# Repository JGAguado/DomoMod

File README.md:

[![GitHub Release][releases-shield]][releases]
[![License][license-shield]](LICENSE)

[![Project Maintenance][maintenance-shield]][maintenance]
[![BuyMeCoffee][buymecoffee-shield]][buymecoffee]

# DomoMod
Mod for ArduLab, directly plugable via the Mod Interface. The DomoMod is designed to enhance the ArduLab functions for domotics aplications: environment monitoring and security systems.

## Project tree

<li><a href="./Design/">Design</a></li>
<li><a href="./Documentation/">Documentation</a></li>

<li><a href="./README.md">README.md</a></li>

[releases-shield]: https://img.shields.io/github/release/JGAguado/DomoMod.svg?style=for-the-badge
[releases]: https://github.com/JGAguado/DomoMod/releases

[license-shield]: https://img.shields.io/badge/License-CC%20BY--NC--SA%204.0-lightgrey.svg?style=for-the-badge

[maintenance-shield]: https://img.shields.io/badge/maintainer-J.%20G.%20Aguado-blue.svg?style=for-the-badge
[maintenance]: https://github.com/JGAguado

[buymecoffee-shield]: https://img.shields.io/badge/buy%20me%20a%20coffee-support-yellow.svg?style=for-the-badge
[buymecoffee]: https://www.buymeacoffee.com/J.G.Aguado

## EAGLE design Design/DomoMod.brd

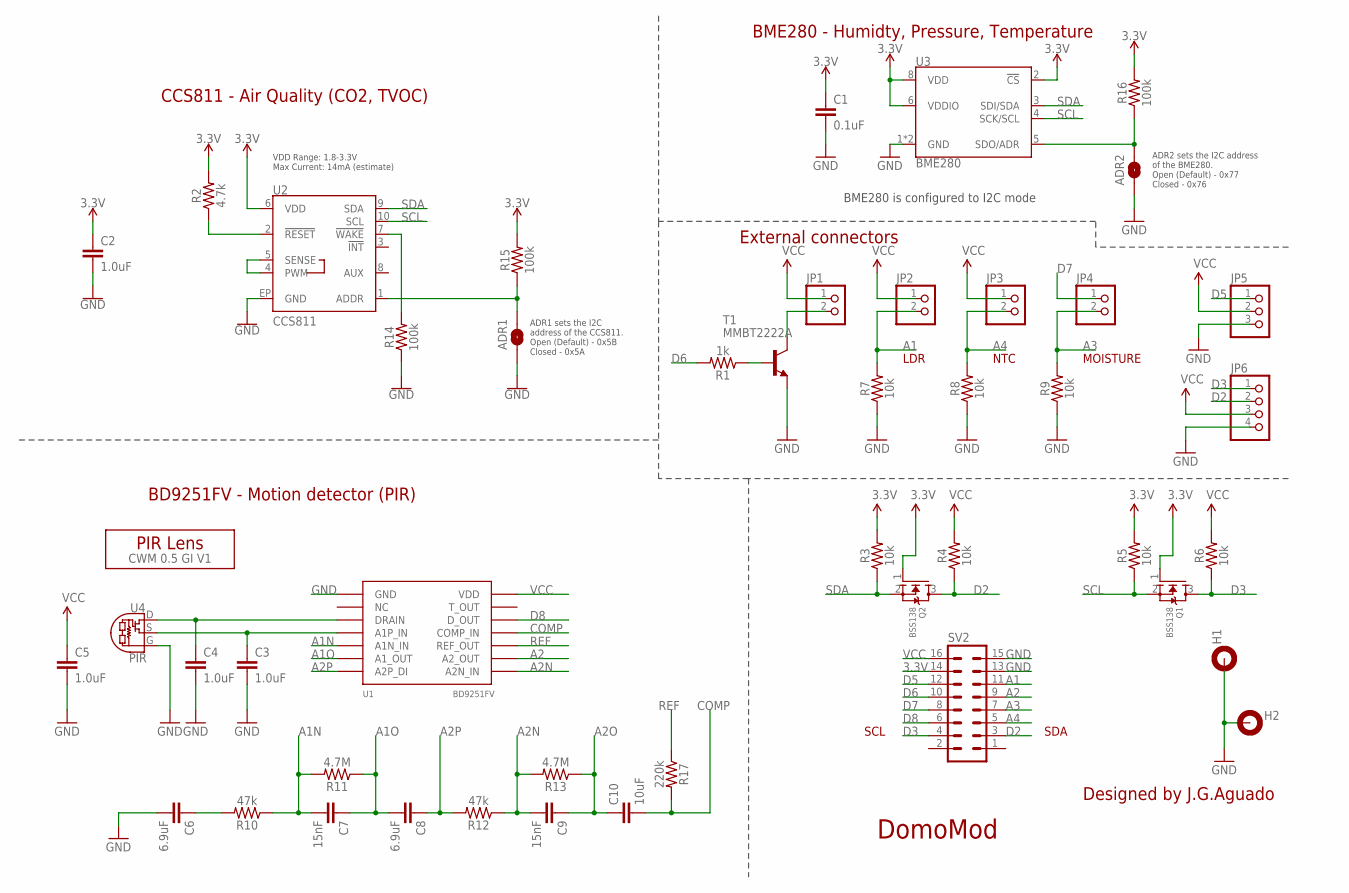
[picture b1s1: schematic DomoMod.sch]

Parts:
ADR1, ADR2: JUMPER-SMT_2_NO_SILK; SMT-JUMPER_2_NO_SILK
C1: 0.1uF; 0603
C2, C3, C4, C5: 1.0uF; 0603
C6, C8: 6.9uF; 0603
C7, C9: 15nF; 0603
C10: 10uF; 0603
H1, H2: MOUNT-PAD-ROUND3.2; 3,2-PAD
JP1, JP2, JP3, JP4: PINHD-1X2; 1X02
JP5: PINHD-1X3; 1X03
JP6: PINHD-1X4; 1X04
Q1, Q2: BSS138; SOT23
R1: 1k; 0603
R2: 4.7k; 0603
R3, R4, R5, R6, R7, R8, R9: 10k; 0603
R10, R12: 47k; 0603
R11, R13: 4.7M; 0603
R14, R15, R16: 100k; 0603
R17: 220k; 0603
SV2: MA08-2
T1: MMBT2222A; SOT23-BEC
U1: BD9251FV; TSSOP-14
U2: CCS811; LGA10
U3: BME280; LGA-8-2.5X2.5
U4: PIR
U$1: CWM 0.5 GI V1; LENS-CWM-0.5-GI-V1

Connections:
3.3V: C1.1, C2.1, Q1.1 (G), Q2.1 (G), R2.2, R3.2, R5.2, R15.2, R16.2, SV2.14, U2.6 (VDD), U3.2 (!CS), U3.6 (VDDIO), U3.8 (VDD)
!RST: R2.1, U2.2 (!RESET!)
!WAKE: R14.2, U2.7 (!WAKE!)
A1: JP2.2, R7.2, SV2.11
A1N: C7.2, R10.1, R11.2, U1.5 (A1N_IN)
A1O: C7.1, C8.2, R11.1, U1.6 (A1_OUT)
A2: SV2.9, U1.9 (A2_OUT)
A2N: C9.2, R12.1, R13.2, U1.8 (A2N_IN)
A2O: C9.1, C10.1, R13.1
A2P: C8.1, R12.2, U1.7 (A2P_DI)
A3: JP4.2, R9.2, SV2.7
A4: JP3.2, R8.2, SV2.5
CCS811_ADDR: ADR1.2, R15.1, U2.1 (ADDR)
COMP: C10.2, R17.2, U1.11 (COMP_IN)
D2: JP6.2, Q2.3 (D), R4.1, SV2.3
D3: JP6.1, Q1.3 (D), R6.1, SV2.4
D5: JP5.1, SV2.12
D6: R1.2, SV2.10
D7: JP4.1, SV2.8
D8: SV2.6, U1.12 (D_OUT)
GND: ADR1.1, ADR2.1, C1.2, C2.2, C3.2, C4.2, C5.2, C6.2, H1.B3,2, H2.B3,2, JP5.3, JP6.4, R7.1, R8.1, R9.1, R14.1, SV2.13, SV2.15, T1.E, U1.1 (GND), U2.EP (GND), U3.1 (GND), U3.7 (GND), U4.G
unnamed: C6.1, R10.2
unnamed: C3.1, U1.4 (A1P_IN), U4.S
unnamed: C4.1, U1.3 (DRAIN), U4.D
unnamed: JP1.2, T1.C
unnamed: R1.1, T1.B
NTC_SENSE: U2.4 (PWM), U2.5 (SENSE)
REF: R17.1, U1.10 (REF_OUT)
SCL: Q1.2 (S), R5.1, U2.10 (SCL), U3.4 (SCK/SCL)
SDA: Q2.2 (S), R3.1, U2.9 (SDA), U3.3 (SDI/SDA)
SDO/ADR: ADR2.2, R16.1, U3.5 (SDO/ADR)
VCC: C5.1, JP1.1, JP2.1, JP3.1, JP5.2, JP6.3, R4.2, R6.2, SV2.16, U1.14 (VDD)

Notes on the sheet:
DomoMod
Designed by J.G.Aguado
VDD Range: 1.8-3.3V Max Current: 14mA (estimate)
CCS811 - Air Quality (CO2, TVOC)
ADR1 sets the I2C address of the CCS811. Open (Default) - 0x5B Closed - 0x5A
ADR2 sets the I2C address of the BME280. Open (Default) - 0x77 Closed - 0x76
BME280 is configured to I2C mode
BME280 - Humidty, Pressure, Temperature
BD9251FV - Motion detector (PIR)
External connectors
SCL
SDA
LDR
NTC
MOISTURE

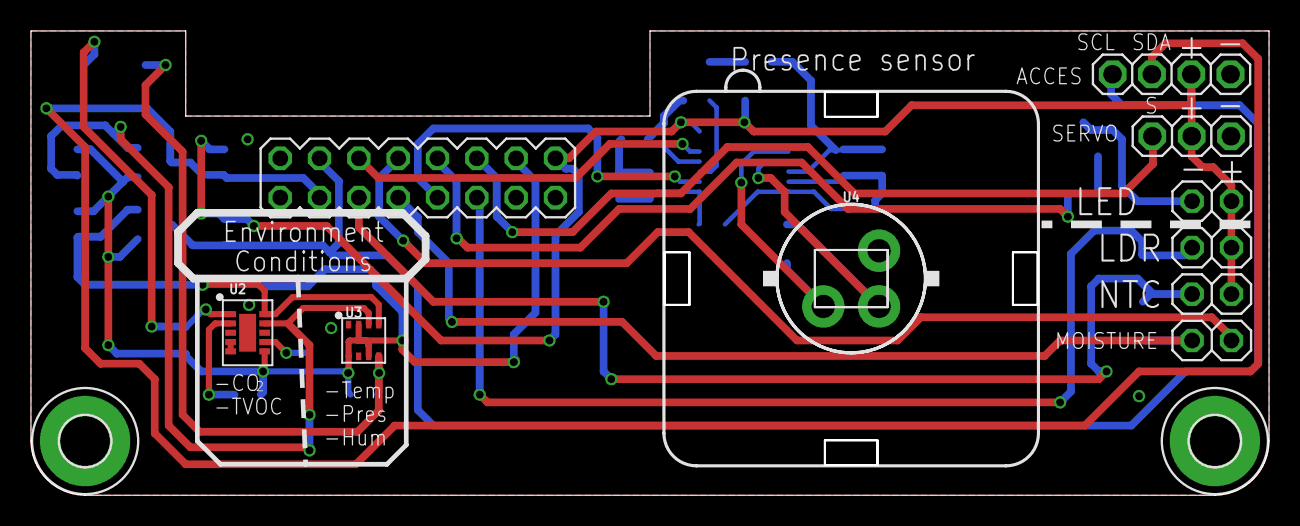
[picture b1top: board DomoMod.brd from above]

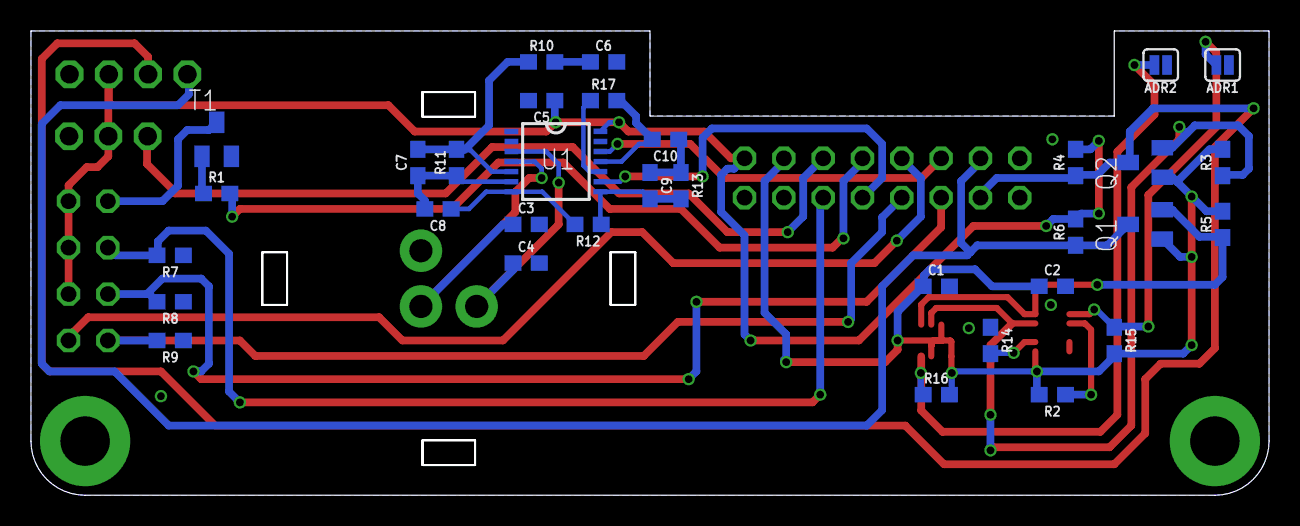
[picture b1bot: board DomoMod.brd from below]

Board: 2 copper layers, 79.9 x 29.9 mm, 46 parts (33 on the bottom side), 32 nets.

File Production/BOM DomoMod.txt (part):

Part Value         Device                    Package              Description                                                MF MPN OC_FARNELL OC_NEWARK PROD_ID   VALUE        
ADR1               JUMPER-SMT_2_NO_SILK      SMT-JUMPER_2_NO_SILK Normally open jumper                                                                                          
ADR2               JUMPER-SMT_2_NO_SILK      SMT-JUMPER_2_NO_SILK Normally open jumper                                                                                          
C1   0.1uF         0.1UF-0603-25V-(+80/-20%) 0603                 0.1µF ceramic capacitors                                                               CAP-00810 0.1uF        
C2   1.0uF         1.0UF-0603-16V-10%        0603                 1µF ceramic capacitors                                                                 CAP-00868 1.0uF        
C3   1.0uF         1.0UF-0603-16V-10%        0603                 1µF ceramic capacitors                                                                 CAP-00868 1.0uF        
C4   1.0uF         1.0UF-0603-16V-10%        0603                 1µF ceramic capacitors                                                                 CAP-00868 1.0uF        
C5   1.0uF         1.0UF-0603-16V-10%        0603                 1µF ceramic capacitors                                                                 CAP-00868 1.0uF        
C6   6.9uF         1.0UF-0603-16V-10%        0603                 1µF ceramic capacitors                                                                 CAP-00868 1.0uF        
C7   15nF          1.0UF-0603-16V-10%        0603                 1µF ceramic capacitors                                                                 CAP-00868 1.0uF        
C8   6.9uF         1.0UF-0603-16V-10%        0603                 1µF ceramic capacitors                                                                 CAP-00868 1.0uF        
C9   15nF          1.0UF-0603-16V-10%        0603                 1µF ceramic capacitors                                                                 CAP-00868 1.0uF        
C10  10uF          1.0UF-0603-16V-10%        0603                 1µF ceramic capacitors                                                                 CAP-00868 1.0uF        
H1                 MOUNT-PAD-ROUND3.2        3,2-PAD              MOUNTING PAD, round                                                                                           
H2                 MOUNT-PAD-ROUND3.2        3,2-PAD              MOUNTING PAD, round                                                                                           
JP1                PINHD-1X2                 1X02                 PIN HEADER                                                                                                    
JP2                PINHD-1X2                 1X02                 PIN HEADER                                                                                                    
JP3                PINHD-1X2                 1X02                 PIN HEADER                                                                                                    
JP4                PINHD-1X2                 1X02                 PIN HEADER                                                                                                    
JP5                PINHD-1X3                 1X03                 PIN HEADER                                                                                                    
JP6                PINHD-1X4                 1X04                 PIN HEADER                                                                                                    
Q1   BSS138        MOSFET-NREFLOW            SOT23                N-Channel Mosfet                                                                                              
Q2   BSS138        MOSFET-NREFLOW            SOT23                N-Channel Mosfet                                                                                              
R1   1k            100KOHM-0603-1/10W-1%     0603                 100kO resistor                                                                         RES-07828 100k         
R2   4.7k          4.7KOHM-0603-1/10W-1%     0603                 4.7kO resistor                                                                         RES-07857 4.7k         
R3   10k           100KOHM-0603-1/10W-1%     0603                 100kO resistor                                                                         RES-07828 100k         
R4   10k           100KOHM-0603-1/10W-1%     0603                 100kO resistor                                                                         RES-07828 100k         
R5   10k           100KOHM-0603-1/10W-1%     0603                 100kO resistor                                                                         RES-07828 100k         
R6   10k           100KOHM-0603-1/10W-1%     0603                 100kO resistor                                                                         RES-07828 100k         
R7   10k           100KOHM-0603-1/10W-1%     0603                 100kO resistor                                                                         RES-07828 100k         
R8   10k           100KOHM-0603-1/10W-1%     0603                 100kO resistor                                                                         RES-07828 100k         
R9   10k           100KOHM-0603-1/10W-1%     0603                 100kO resistor                                                                         RES-07828 100k         
R10  47k           100KOHM-0603-1/10W-1%     0603                 100kO resistor                                                                         RES-07828 100k         
R11  4.7M          100KOHM-0603-1/10W-1%     0603                 100kO resistor                                                                         RES-07828 100k         
R12  47k           100KOHM-0603-1/10W-1%     0603                 100kO resistor                                                                         RES-07828 100k         
R13  4.7M          100KOHM-0603-1/10W-1%     0603                 100kO resistor                                                                         RES-07828 100k         
R14  100k          100KOHM-0603-1/10W-1%     0603                 100kO resistor                                                                         RES-07828 100k         
R15  100k          100KOHM-0603-1/10W-1%     0603                 100kO resistor                                                                         RES-07828 100k         
R16  100k          100KOHM-0603-1/10W-1%     0603                 100kO resistor                                                                         RES-07828 100k         
R17  220k          100KOHM-0603-1/10W-1%     0603                 100kO resistor                                                                         RES-07828 100k         
SV1                MA08-2                    MA08-2               PIN HEADER                                                        unknown    unknown                          
T1   MMBT2222A     BC808-NPN-SOT23-BEC       SOT23-BEC            NPN Transistror                                                                                               
U$1  CWM 0.5 GI V1 PIR-LENSCWM-0.5-GI-V1     LENS-CWM-0.5-GI-V1                                                                                                    CWM 0.5 GI V1
U1   BD9251FV      BD9251FV                  TSSOP-14             Amplifier for Pyroelectric Infrared Sensor                                                                    
U2   CCS811        CCS811PRODUCTION          LGA10                AMS CCS811 &ndash; I2C Digital Gas Sensor                                              IC-13607  CCS811       
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
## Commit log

2018-01-10 Added schematics for Temp/Hum and barometric pressure sensor.
2018-01-13 SCH: -Components placed and connected -Documented BRD: -Components placed -100% routed -DRC passed
2018-01-14 GERBER files
2018-01-14 Added BOM and Centroid file
2018-01-17 Update gerber for production
2018-01-30 Component replacement: NCS36000 -> BD9251FV
2018-02-01 BRD and Production files updated for component BD9251FV
2018-02-03 Added Schematics.pdf
2018-02-09 Fixed connector interface (rows were changed)
2018-02-09 Updated BOM
2018-02-09 Updated centroid file
2018-02-22 Updated Production/DomoMod.GTL
2018-05-02 Updated design files
2018-05-02 Updated production files
2018-05-02 Updated documentation
2022-04-15 Updated structure

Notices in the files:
parts and their libraries:
SparkFun-Capacitors: Licensing: Creative Commons ShareAlike 4.0 International - https://creativecommons.org/licenses/by-sa/4.0
